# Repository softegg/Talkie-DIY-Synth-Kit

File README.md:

# Talkie-DIY-Synth-Kit
 Talkie is a DIY Handheld Virtual Analog Music Synthesizer Kit designed by Tina Belmont for the X-Days 2025 event at X-Hain hack+make space, Friedrichshain, Berlin.
 
 This project is based on the Vectorscope Synth ( https://github.com/softegg/Vectorscope-Synth ) made for a Hackaday Berlin 2024 workshop, which was based on the Stylish Trucker Belt Buckle Music Synthesizer ( https://github.com/softegg/Stylish-Trucker-Belt-Synthesizer ) originally made for MAGwest in 2018. Please find the Arduino source code in those projects.
 
 This project is licensed as non-commercial use only. Individuals can use the code and designs to make and modify their own synthesizers, but they cannot sell them without a license from me.
 
 No warranty of correctness or suitablility or safety is provided or honored for this project. Use at your own risk.

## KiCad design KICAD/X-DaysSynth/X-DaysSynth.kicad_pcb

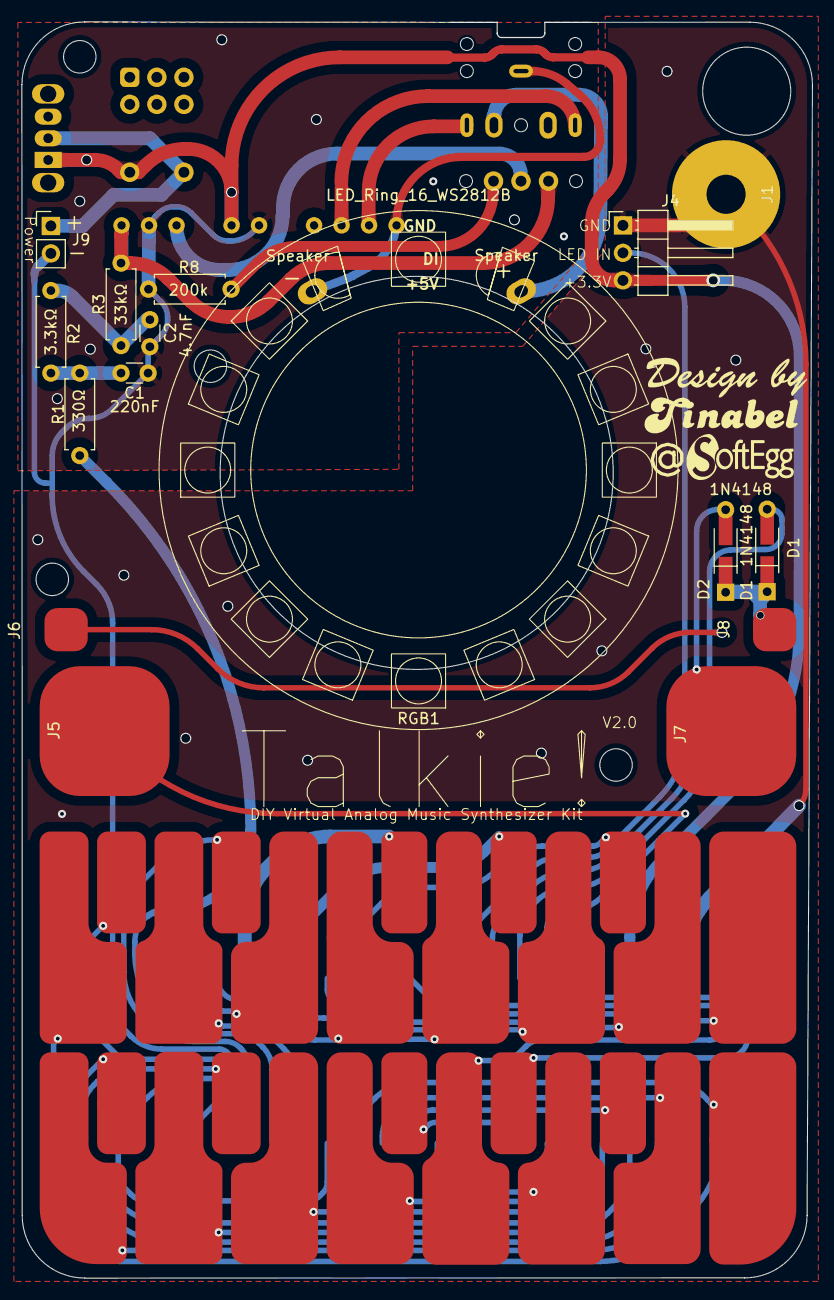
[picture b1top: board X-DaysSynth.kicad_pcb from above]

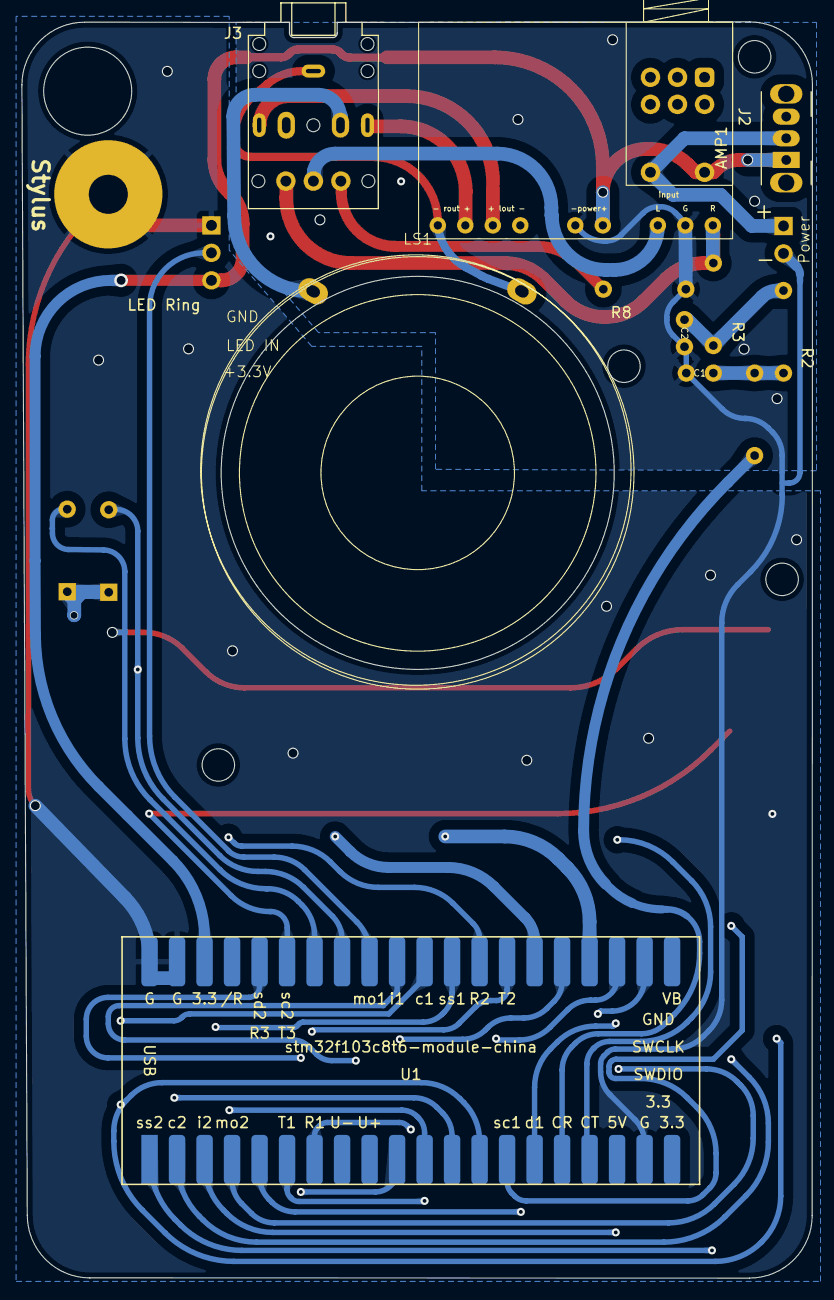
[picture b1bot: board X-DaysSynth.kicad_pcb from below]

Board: 2 copper layers, 72.9 x 115.9 mm, 23 parts (6 on the bottom side), 45 nets.

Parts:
AMP1: GF1002-PAM8403_Amplifier_Module_w_bottom_pins
C1: 220nF; C_Disc_D3.0mm_W1.6mm_P2.50mm
C2: 4.7nF; C_Disc_D3.0mm_W1.6mm_P2.50mm
D1, D2: 1N4148; D_DO-35_SOD27_P7.62mm_Horizontal+SMD
J1: STYLUS; SmallRoundTouchPad
J2: Power Switch; SW_Slide_SPDT_Angled_CK_OS102011MA1Q
J3: AudioJackX_Ground_Switch; Jack_3.5mm_PJ-307A_Horizontal
J4: LED Ring; PinHeader_1x03_P2.54mm_Horizontal
J5: PATCH SELECT; SmallRoundTouchPad
J6: WRITE PATCH; SmallRoundTouchPad
J7: PARAM SELECT; SmallRoundTouchPad
J8: MODE; SmallRoundTouchPad
J9: Power; PinHeader_1x02_P2.54mm_Vertical
KB1: StylusKeyboardA; StylusKeyboard_noVias
LS1: Speaker; Speaker 40mm
NT1: NetTie_3; NetTie-3_SMD_Pad0.5mm
R1: 330Ω; R_Axial_DIN0207_L6.3mm_D2.5mm_P7.62mm_Horizontal
R2: 3.3kΩ; R_Axial_DIN0207_L6.3mm_D2.5mm_P7.62mm_Horizontal
R3: 33kΩ; R_Axial_DIN0207_L6.3mm_D2.5mm_P7.62mm_Horizontal
R8: 200k; R_Axial_DIN0207_L6.3mm_D2.5mm_P7.62mm_Horizontal
RGB1: LED_Ring_16_WS2812B; LED RING 16 WS2812B 48mm
U1: stm32f103c8t6-module-china; stm32f103c8t6-module-china-smd

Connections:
+3.3V: AMP1.6 (POWER+), AMP1.16 (SWITCH1), J2.1, J4.3, U1.38 (3V3)
/A0: KB1.9 (A0), U1.10 (A15/JTDI)
/A1: KB1.21 (A1), U1.27 (A2/U2TX)
/A#0: KB1.10 (A#0), U1.11 (B3/JTDO)
/A#1: KB1.22 (A#1), U1.28 (A3/U2RX)
/AUDIO_LOW: AMP1.9 (R), J3.I (IN), R3.1
/B0: KB1.11 (B0), U1.12 (B4/JnTRST)
/B1: KB1.23 (B1), U1.29 (A4/NSS1)
/C0: KB1.0 (C0), U1.1 (B12/NSS2)
/C1: KB1.12 (C1), U1.13 (B5)
/C2: KB1.24 (C2), U1.30 (A5/SCK1)
/C#0: KB1.1 (C#0), U1.2 (B13/SCK2)
/C#1: KB1.13 (C#1), U1.14 (B6/SCL1a/U1TXb)
/D0: KB1.2 (D0), U1.3 (B14/MISO2)
/D1: KB1.14 (D1), U1.15 (B7/SDA1a/U1RXb)
/D#0: KB1.3 (D#0), U1.4 (B15/MOSI2)
/D#1: KB1.15 (D#1), U1.17 (B9/SDA1b/CANTX)
/DGND: J1.1, J4.1, NT1.1, U1.19 (GND), U1.39 (GND), U1.40 (GND)
/E0: KB1.4 (E0), U1.5 (A8/MCO)
/E1: KB1.16 (E1), U1.22 (C13)
/F0: KB1.5 (F0), U1.6 (A9/U1TXa)
/F1: KB1.17 (F1), U1.23 (C14/OSC32_IN)
/F#0: KB1.6 (F#0), U1.7 (A10/U1RXa)
/F#1: KB1.18 (F#1), U1.24 (C15/OSC32_OUT)
/G0: KB1.7 (G0), U1.31 (A6/MISO1)
/G1: KB1.19 (G1), U1.25 (A0/WKUP)
/G#0: KB1.8 (G#0), U1.36 (B11/SDA2/U3RX)
/G#1: KB1.20 (G#1), U1.26 (A1)
/GND-IN: J9.2, NT1.2
/LED_DIN: J4.2, U1.32 (A7/MOSI1)
/PARAM: D2.2 (A), J7.1, U1.33 (B0)
/PATCH: J5.1, U1.35 (B10/SCL2/U3TX)
/PWM_OUT: R1.2, U1.16 (B8/SCL1b/CANRX)
/WRITE: D1.2 (A), J6.1, U1.34 (B1)
GNDA: AMP1.5 (POWER-), AMP1.8 (G), C1.2, C2.2, NT1.3, R8.2
unnamed: AMP1.7 (L), J3.C (COM)
unnamed: AMP1.3 (LOUT+), J3.T
unnamed: AMP1.2 (ROUT+), J3.R
unnamed: AMP1.1 (ROUT-), J3.G, LS1.1
unnamed: AMP1.17 (SWITCH2), J2.2, J9.1
unnamed: C1.1, R1.1, R2.2
unnamed: C2.1, R2.1, R3.2
unnamed: D1.1 (K), D2.1 (K), J8.1
unnamed: J3.O (OUT), R8.1
unnamed: J3.RN, LS1.2

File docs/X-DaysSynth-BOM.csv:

"Id";"Designator";"Footprint";"Quantity";"Designation";"Supplier and ref";
1;"J9";"PinHeader_1x02_P2.54mm_Vertical";1;"Power";;;
2;"J3";"Jack_3.5mm_PJ-307A_Horizontal";1;"AudioJackX_Ground_Switch";;;
3;"R3";"R_Axial_DIN0207_L6.3mm_D2.5mm_P7.62mm_Horizontal";1;"33kΩ";;;
4;"J8";"SmallRoundTouchPad";1;"MODE";;;
5;"J6";"SmallRoundTouchPad";1;"WRITE PATCH";;;
6;"KB1";"StylusKeyboard_noVias";1;"StylusKeyboardA";;;
7;"C1";"C_Disc_D3.0mm_W1.6mm_P2.50mm";1;"220nF";;;
8;"J5";"SmallRoundTouchPad";1;"PATCH SELECT";;;
9;"J4";"PinHeader_1x03_P2.54mm_Horizontal";1;"LED Ring";;;
10;"R2";"R_Axial_DIN0207_L6.3mm_D2.5mm_P7.62mm_Horizontal";1;"3.3kΩ";;;
11;"R8";"R_Axial_DIN0207_L6.3mm_D2.5mm_P7.62mm_Horizontal";1;"200k";;;
12;"D2,D1";"D_DO-35_SOD27_P7.62mm_Horizontal+SMD";2;"1N4148";;;
13;"RGB1";"LED RING 16 WS2812B 48mm";1;"LED_Ring_16_WS2812B";;;
14;"J7";"SmallRoundTouchPad";1;"PARAM SELECT";;;
15;"R1";"R_Axial_DIN0207_L6.3mm_D2.5mm_P7.62mm_Horizontal";1;"330Ω";;;
16;"J1";"SmallRoundTouchPad";1;"STYLUS";;;
17;"C2";"C_Disc_D3.0mm_W1.6mm_P2.50mm";1;"4.7nF";;;
18;"U1";"stm32f103c8t6-module-china-smd";1;"stm32f103c8t6-module-china";;;
19;"AMP1";"GF1002-PAM8403_Amplifier_Module_w_bottom_pins";1;"~";;;
20;"J2";"SW_Slide_SPDT_Angled_CK_OS102011MA1Q";1;"Power Switch";;;
21;"LS1";"Speaker 40mm";1;"Speaker";;;

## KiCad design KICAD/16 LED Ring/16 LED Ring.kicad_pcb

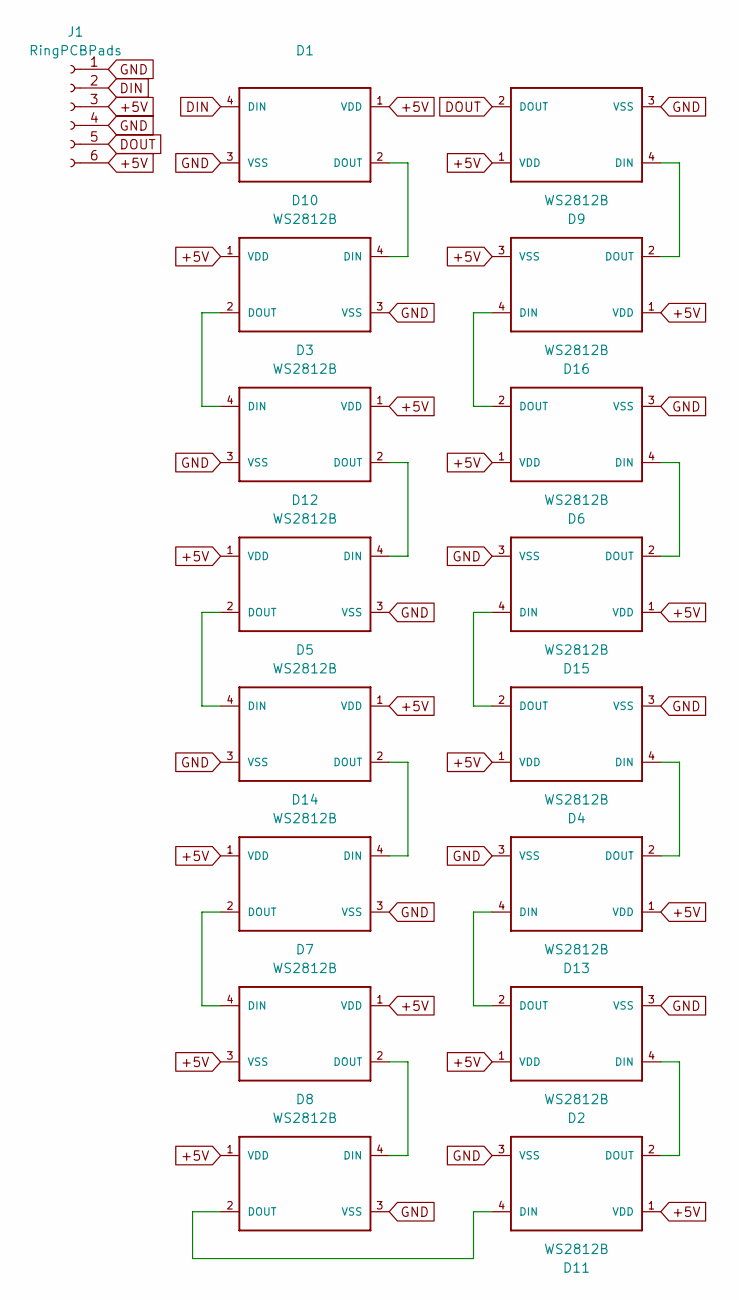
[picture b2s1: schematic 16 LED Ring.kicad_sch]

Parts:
D1, D2, D3, D4, D5, D6, D7, D8, D9, D10, D11, D12, D13, D14, D15, D16: WS2812B
J1: RingPCBPads; LED RING 16 WS2812B 48mm standalone

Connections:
+5V: D1.1 (VDD), D2.1 (VDD), D3.1 (VDD), D4.1 (VDD), D5.1 (VDD), D6.1 (VDD), D7.1 (VDD), D7.3 (VSS), D8.1 (VDD), D9.1 (VDD), D10.1 (VDD), D11.1 (VDD), D12.1 (VDD), D13.1 (VDD), D14.1 (VDD), D15.1 (VDD), D16.1 (VDD), D16.3 (VSS), J1.3, J1.6
DIN: D1.4 (DIN), J1.2
DOUT: D9.2 (DOUT), J1.5
GND: D1.3 (VSS), D2.3 (VSS), D3.3 (VSS), D4.3 (VSS), D5.3 (VSS), D6.3 (VSS), D8.3 (VSS), D9.3 (VSS), D10.3 (VSS), D11.3 (VSS), D12.3 (VSS), D13.3 (VSS), D14.3 (VSS), D15.3 (VSS), J1.1, J1.4
unnamed: D1.2 (DOUT), D10.4 (DIN)
unnamed: D7.2 (DOUT), D8.4 (DIN)
unnamed: D3.4 (DIN), D10.2 (DOUT)
unnamed: D8.2 (DOUT), D11.4 (DIN)
unnamed: D2.4 (DIN), D11.2 (DOUT)
unnamed: D3.2 (DOUT), D12.4 (DIN)
unnamed: D5.4 (DIN), D12.2 (DOUT)
unnamed: D2.2 (DOUT), D13.4 (DIN)
unnamed: D4.4 (DIN), D13.2 (DOUT)
unnamed: D5.2 (DOUT), D14.4 (DIN)
unnamed: D7.4 (DIN), D14.2 (DOUT)
unnamed: D4.2 (DOUT), D15.4 (DIN)
unnamed: D6.4 (DIN), D15.2 (DOUT)
unnamed: D6.2 (DOUT), D16.4 (DIN)
unnamed: D9.4 (DIN), D16.2 (DOUT)

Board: 2 copper layers, 17 parts (0 on the bottom side), 19 nets, no tracks yet.

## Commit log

2025-09-28 As Manufactured for X-Days
2025-09-28 Updated manuals
2025-09-28 Updated PDF
    Updated PDF with page numbers and additional bodge information from indesign file
2025-09-28 Redid readme after having to force overwrite the one I did on Github because I can't seem to merge for some reason.
2025-10-19 LED ring 3d models updated PCB and schematic Logo Text first draft enclosures 3d models
